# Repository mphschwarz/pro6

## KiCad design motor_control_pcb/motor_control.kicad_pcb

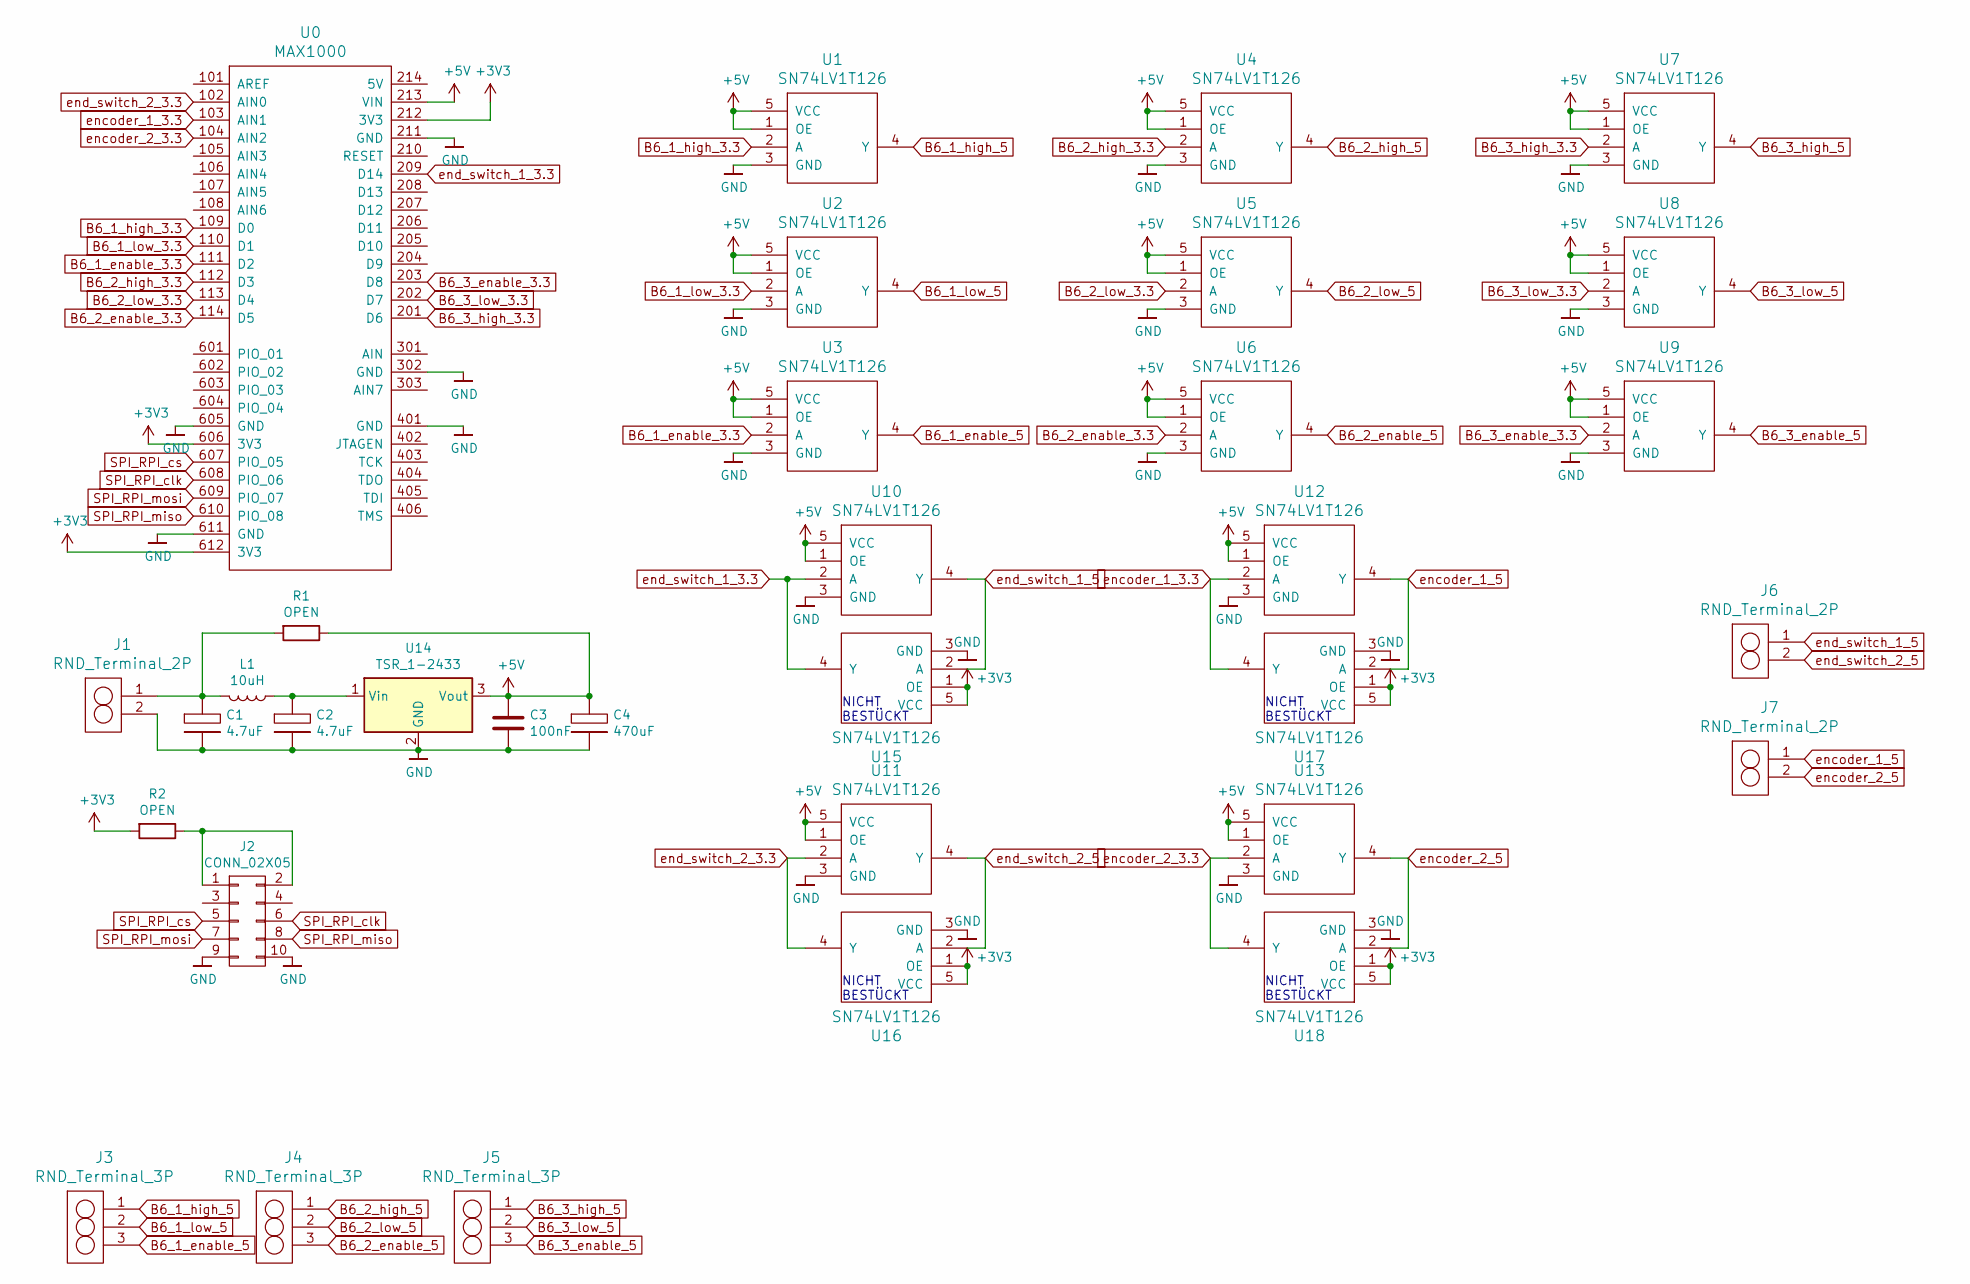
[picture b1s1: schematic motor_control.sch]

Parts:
C1, C2: 4.7uF; C_1206_HandSoldering
C3: 100nF; C_0805_HandSoldering
C4: 470uF; C_1206_HandSoldering
J1, J6, J7: RND_Terminal_2P; RND_Terminal_2P_381
J2: CONN_02X05; IDC_Header_Straight_10pins
J3, J4, J5: RND_Terminal_3P; RND_Terminal_3P_381
L1: 10uH; L_Wuerth_4020_Handsoldering
R1, R2: OPEN; R_1206_HandSoldering
U0: MAX1000
U1, U2, U3, U4, U5, U6, U7, U8, U9, U10, U11, U12, U13, U15, U16, U17, U18: SN74LV1T126; SOT-23-5_Handsoldering
U14: TSR_1-2433; TSR_2-2450

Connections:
+3V3: R2.2, U0.212 (3V3), U0.606 (3V3), U0.612 (3V3), U15.1 (OE), U15.5 (VCC), U16.1 (OE), U16.5 (VCC), U17.1 (OE), U17.5 (VCC), U18.1 (OE), U18.5 (VCC)
+5V: C3.1, C4.1, R1.1, U0.213 (VIN), U1.1 (OE), U1.5 (VCC), U2.1 (OE), U2.5 (VCC), U3.1 (OE), U3.5 (VCC), U4.1 (OE), U4.5 (VCC), U5.1 (OE), U5.5 (VCC), U6.1 (OE), U6.5 (VCC), U7.1 (OE), U7.5 (VCC), U8.1 (OE), U8.5 (VCC), U9.1 (OE), U9.5 (VCC), U10.1 (OE), U10.5 (VCC), U11.1 (OE), U11.5 (VCC), U12.1 (OE), U12.5 (VCC), U13.1 (OE), U13.5 (VCC), U14.3 (Vout)
B6_1_enable_3.3: U0.111 (D2), U3.2 (A)
B6_1_enable_5: J3.3, U3.4 (Y)
B6_1_high_3.3: U0.109 (D0), U1.2 (A)
B6_1_high_5: J3.1, U1.4 (Y)
B6_1_low_3.3: U0.110 (D1), U2.2 (A)
B6_1_low_5: J3.2, U2.4 (Y)
B6_2_enable_3.3: U0.114 (D5), U6.2 (A)
B6_2_enable_5: J4.3, U6.4 (Y)
B6_2_high_3.3: U0.112 (D3), U4.2 (A)
B6_2_high_5: J4.1, U4.4 (Y)
B6_2_low_3.3: U0.113 (D4), U5.2 (A)
B6_2_low_5: J4.2, U5.4 (Y)
B6_3_enable_3.3: U0.203 (D8), U9.2 (A)
B6_3_enable_5: J5.3, U9.4 (Y)
B6_3_high_3.3: U0.201 (D6), U7.2 (A)
B6_3_high_5: J5.1, U7.4 (Y)
B6_3_low_3.3: U0.202 (D7), U8.2 (A)
B6_3_low_5: J5.2, U8.4 (Y)
GND: C1.2, C2.2, C3.2, C4.2, J1.2, J2.9, J2.10, U0.211 (GND), U0.302 (GND), U0.401 (GND), U0.605 (GND), U0.611 (GND), U1.3 (GND), U2.3 (GND), U3.3 (GND), U4.3 (GND), U5.3 (GND), U6.3 (GND), U7.3 (GND), U8.3 (GND), U9.3 (GND), U10.3 (GND), U11.3 (GND), U12.3 (GND), U13.3 (GND), U14.2 (GND), U15.3 (GND), U16.3 (GND), U17.3 (GND), U18.3 (GND)
unnamed: C1.1, J1.1, L1.2, R1.2
unnamed: C2.1, L1.1, U14.1 (Vin)
unnamed: J2.1, J2.2, R2.1
SPI_RPI_clk: J2.6, U0.608 (PIO_06)
SPI_RPI_cs: J2.5, U0.607 (PIO_05)
SPI_RPI_miso: J2.8, U0.610 (PIO_08)
SPI_RPI_mosi: J2.7, U0.609 (PIO_07)
encoder_1_3.3: U0.103 (AIN1), U12.2 (A), U17.4 (Y)
encoder_1_5: J7.1, U12.4 (Y), U17.2 (A)
encoder_2_3.3: U0.104 (AIN2), U13.2 (A), U18.4 (Y)
encoder_2_5: J7.2, U13.4 (Y), U18.2 (A)
end_switch_1_3.3: U0.209 (D14), U10.2 (A), U15.4 (Y)
end_switch_1_5: J6.1, U10.4 (Y), U15.2 (A)
end_switch_2_3.3: U0.102 (AIN0), U11.2 (A), U16.4 (Y)
end_switch_2_5: J6.2, U11.4 (Y), U16.2 (A)

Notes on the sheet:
NICHT BESTÜCKT

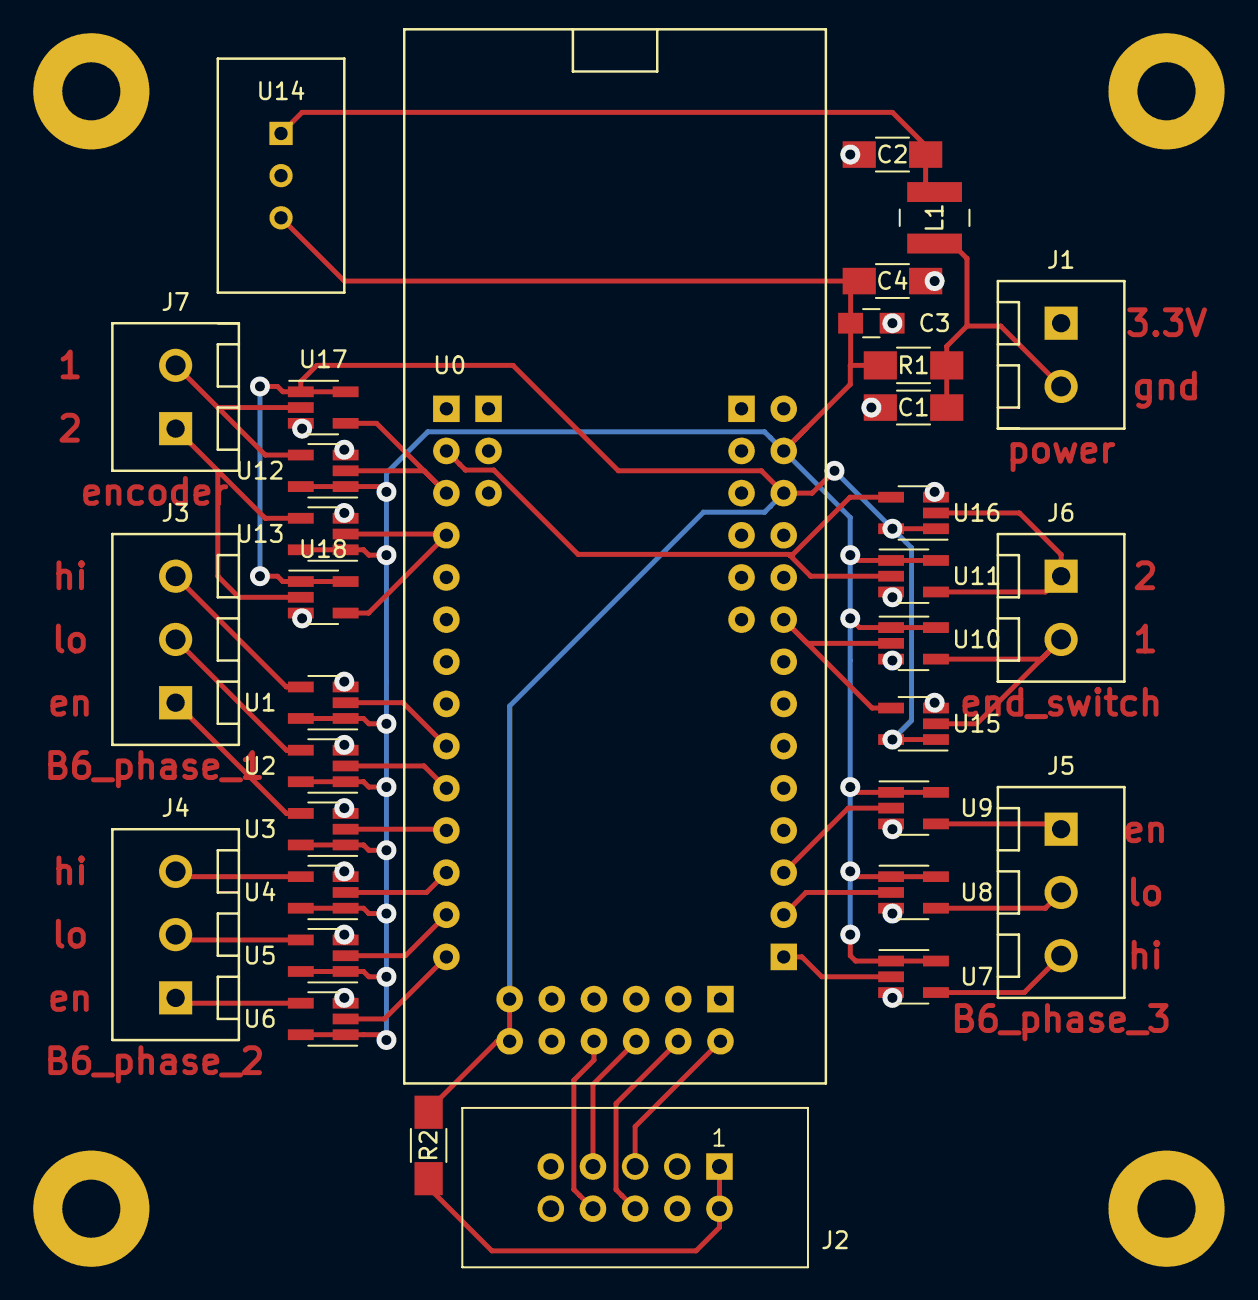
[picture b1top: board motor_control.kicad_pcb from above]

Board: 2 copper layers, 33 parts (0 on the bottom side), 36 nets.

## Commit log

2019-05-02 added all the files
2019-05-02 vias korrigiert
2019-05-02 moved connectors
2019-05-08 github don't fail me now
2019-05-13 projektwoche fertig
2019-07-22 vector_modulation_works
2019-07-22 vector_modulation actually works
2019-07-26 ready for testing
2019-07-31 before overhaul
2019-08-02 overhauled
2019-08-03 ready for meeting
2019-08-04 move to win
2019-08-09 demonstraton success
2019-08-11 hopefully final version
2019-08-13 before final overhaul
2019-08-14 overhaul works
2019-08-15 hopefully final commit for source code
2019-08-15 removed large files
2019-08-16 updated plots
2019-08-16 final clean up
